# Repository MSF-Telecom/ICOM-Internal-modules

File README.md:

# ICOM Internal modules

A collection of custom internal modules for ICOM IC-F5060/6060 radios.

## Pinouts

The IC-F5060/6060 and IC-F3162T radios have two 40-pin accessory connectors (J1 and J2). They mate with a [Panasonic P5 Series P5K AXK640347YG](https://na.industrial.panasonic.com/products/connectors/board-board-connectors/lineup/narrow-fine-pitch-connectors/series/82696/model/83045) connector.  
You can find a KiCAD Library for J1 and J2 to make your own modules [here](./CAD-Libs/ICOM-J1-J2). The pinouts are as follows (from the service manual) :

### J1

```ascii
           ┌─────╮
      NC   │40  1│   NC
     GND   │39  2│   GND
     +5V   │38  3│   PTTI
     VCC   │37  4│   PTTO
      NC   │36  5│   MCOT
   MMUTI   │35  6│   NC
    AFON   │34  7│   MCIN
    BEPO   │33  8│   NC
    RMUT   │32  9│   NC
    DISC   │31 10│   NC
   AFOUT   │30 11│   NC
      NC   │29 12│   BUSY
     REM   │28 13│   SIGO
     CCS   │27 14│   OPT1/RxD
    CIRQ   │26 15│   OPT2/TxD
      NC   │25 16│   OPT3
     CSO   │24 17│   GND
     CSI   │23 18│   OPV3
     CCK   │22 19│   OPV2
      NC   │21 20│   OPV1
           └─────╯
```

### J2

```ascii
           ┌─────╮
     DIF   │40  1│   DIF
     GND   │39  2│   GND
     +5V   │38  3│   NC
      8V   │37  4│   NC
      NC   │36  5│   NC
      NC   │35  6│   DMO
      NC   │34  7│   NC
      NC   │33  8│   DMI
      NC   │32  9│   NC
    DISC   │31 10│   VREF
      NC   │30 11│   NC
    DAFO   │29 12│   NC
      NC   │28 13│   NC
     CCS   │27 14│   OPT1 (DPDN)
    CIRQ   │26 15│   OPT2 (DRES)
      NC   │25 16│   OPT3 (DRES)
     CSO   │24 17│   GND
     CSI   │23 18│   NC
     CCK   │22 19│   GND
     GND   │21 20│   GND
           └─────╯
```

## Acknowledgements

Made with ❤️, lots of ☕️, and lack of 🛌  
Published under CreativeCommons BY-SA 4.0

This work is licensed under a [Creative Commons Attribution-ShareAlike 4.0 International License](http://creativecommons.org/licenses/by-sa/4.0/).

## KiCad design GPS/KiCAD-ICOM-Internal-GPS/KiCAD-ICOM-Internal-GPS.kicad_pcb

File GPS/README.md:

# GPS Module

All the files and R&D data for a custom GPS module.

## Module Design Specifications

A.  Must have  

  1. UT-126H form factor (20x35mm)
  2. UART NMEA GPS module with 4800/9600 baud rate
  3. 5V Supply compatible
  4. 5V Antenna supply
  5. UFL Antenna connector
  6. Test pads for VCC, GND, TX, RX and PPS

B.  Nice to have

  1. Switchable antenna supply
  2. Backup battery circuitry
  3. Antenna short circuit detection & protection

C.  Optional

  1. Antenna connection detection
  2. Additional 2.54mm pitch header with VCC, GND, UART, PPS and I2C
  3. PPS LED
  4. TX/RX LEDs

## Module Design Choices

### v1.0

#### Requirements

- PCB
  - 2 layer
  - Test pads on user visible side (satisfies A6)
  - 20x35mm form factor (satisfies A1)
  - Silk screen on user visible side with checkable baud rate options
- Connectors
  - UFL Antenna connector (satisfies A5)
  - 2.54mm pitch header with VCC, GND, UART, PPS and I2C (satisfies C2)
- Battery backup with 6.8mm SDM 3V rechargeable lithium cell (satisfies B2)
- GPS Module : [u-blox MAX-M10](https://www.u-blox.com/en/product/max-m10-series?legacy=Current#Documentation-&-resources) (can satisfy A1, A2, A3 with regulator, A4, B1, B2, B3 and C1)
- LEDs on user visible side (satisfies C3 and C4)
- No antenna short circuit detection (does not satisfy B3 or C1)
- Constant 5V antenna supply (satisfies A4, but not B1)

#### Component choice

- [u-blox MAX-M10](https://www.u-blox.com/en/product/max-m10-series?legacy=Current#Documentation-&-resources)
- Battery : [SEIKO INSTRUMENTS MS518SE-FL35E](https://www.farnell.com/datasheets/3115182.pdf) ([Farnell](https://be.farnell.com/en-BE/seiko-instruments/ms518se-fl35e/battery-button-lithium-3-4mah/dp/3534575))
- U.FL : [HIROSE(HRS) U.FL-R-SMT-1(10)](https://www.farnell.com/datasheets/2691132.pdf) ([Farnell](https://be.farnell.com/en-BE/hirose-hrs/u-fl-r-smt-1-10/rf-coaxial-u-fl-straight-jack/dp/1688077))
- C1, C2 : [0603B105K250NT](https://www.lcsc.com/datasheet/lcsc_datasheet_2304140030_FH--Guangdong-Fenghua-Advanced-Tech-0603B105K250NT_C59302.pdf)
- L1 (Antenna supply inductor, 27nH) : [Murata LQG15HS27NJ02D](https://www.mouser.be/datasheet/2/281/1/JELF243B_0010-1699614.pdf)
- C4, C5, C6 (Antenna supply filter, 10nF, 16V, X7R) : [CC0603KRX7R0BB103](https://www.lcsc.com/datasheet/lcsc_datasheet_2304140030_YAGEO-CC0603KRX7R0BB103_C107059.pdf)
- 3.3V Regulator : [SPX5205M5-L-3-3/TR](https://www.lcsc.com/datasheet/lcsc_datasheet_2304140030_MaxLinear-SPX5205M5-L-3-3-TR_C6864.pdf)
- D1 : [RB551V-40](https://www.lcsc.com/datasheet/lcsc_datasheet_2308281443_hongjiacheng-RB551V-40_C7502699.pdf)
- D2 : [KINGBRIGHT KPTR-3216SURCK](https://www.farnell.com/datasheets/2045968.pdf)
- D3 : [XL-3216SURC](https://www.lcsc.com/datasheet/lcsc_datasheet_2402181505_XINGLIGHT-XL-3216SURC_C965822.pdf)
- D4, D5 : [XL-3216UOC](https://www.lcsc.com/datasheet/lcsc_datasheet_2402181505_XINGLIGHT-XL-3216UOC_C965823.pdf)
- R1 : [ERJPA3J100V](https://www.lcsc.com/product-detail/Chip-Resistor-Surface-Mount_PANASONIC-ERJPA3J100V_C441879.html)
- R2, R3, R4 : [CR0603-FX-3301ELF](https://www.lcsc.com/datasheet/lcsc_datasheet_2304140030_BOURNS-CR0603-FX-3301ELF_C203527.pdf)
- R5, R6, R7, R8 : [RC0603JR-07220RL](https://www.lcsc.com/datasheet/lcsc_datasheet_2304140030_YAGEO-RC0603JR-07220RL_C114683.pdf)

#### Cost breakdown

> Cost for one unit at 100pcs MOQ, without PCBA

##### Full prototype with debug LEDs

| Component                                  | Source | Cost ($) | Amount | Total ($) |
|--------------------------------------------|--------|----------|--------|-----------|
| PCB                                        | JLCPCB | 0.141    | 1      | 0.141     |
| LQG15HS27NJ02DLQG15HS27NJ02D 27nH inductor | LCSC   | 0.0065   | 1      | 0.0065    |
| U.FL-R-SMT-1(10) UFL connector             | LCSC   | 0.0.1177 | 1      | 0.1615    |
| SPX5205M5-L-3-3/TR 3.3V LDO regulator      | LCSC   | 0.1209   | 1      | 0.1209    |
| 0603B105K250NT 1uF 25V capacitor           | LCSC   | 0.0053   | 2      | 0.0106    |
| CC0603KRX7R0BB103 10nF 16V capacitor       | LCSC   | 0.0041   | 4      | 0.0164    |
| RC0603JR-07220RL 220 Ohm resistor          | LCSC   | 0.001    | 4      | 0.0040    |
| CR0603-FX-3301ELF 3.3k Ohm resistor        | LCSC   | 0.0062   | 3      | 0.0186    |
| ERJPA3J100V 10 Ohm resistor                | LCSC   | 0.0193   | 1      | 0.0193    |
| APTR3216SURCK Through-PCB LED              | LCSC   | 0.1032   | 1      | 0.1032    |
| MAX-M10S-00B GPS module                    | Mouser | 11.48    | 1      | 11.48     |
| AXK640347YG Connector                      | Mouser | 1.60     | 1      | 1.60      |
| MS518SE-FL35E Battery                      | Farnell| 2.15     | 1      | 2.15      |
| RB551V-40 Diode                            | LCSC   | 0.018    | 1      | 0.018     |
| XL-3216SURC Red LED                        | LCSC   | 0.0082   | 1      | 0.0082    |
| XL-3216UOC Orange LED                      | LCSC   | 0.0092   | 2      | 0.0184    |
|                                            |        |          |        |           |
| **Total**                                  |        |          |        | 15.8766   |

##### Integration prototype with battery backup

| Component                                  | Source | Cost ($) | Amount | Total ($) |
|--------------------------------------------|--------|----------|--------|-----------|
| PCB                                        | JLCPCB | 0.141    | 1      | 0.141     |
| LQG15HS27NJ02DLQG15HS27NJ02D 27nH inductor | LCSC   | 0.0065   | 1      | 0.0065    |
| U.FL-R-SMT-1(10) UFL connector             | LCSC   | 0.0.1177 | 1      | 0.1615    |
| SPX5205M5-L-3-3/TR 3.3V LDO regulator      | LCSC   | 0.1209   | 1      | 0.1209    |
| 0603B105K250NT 1uF 25V capacitor           | LCSC   | 0.0053   | 2      | 0.0106    |
| CC0603KRX7R0BB103 10nF 16V capacitor       | LCSC   | 0.0041   | 4      | 0.0164    |
| RC0603JR-07220RL 220 Ohm resistor          | LCSC   | 0.001    | 1      | 0.0010    |
| CR0603-FX-3301ELF 3.3k Ohm resistor        | LCSC   | 0.0062   | 3      | 0.0186    |
| ERJPA3J100V 10 Ohm resistor                | LCSC   | 0.0193   | 1      | 0.0193    |
| APTR3216SURCK Through-PCB LED              | LCSC   | 0.1032   | 1      | 0.1032    |
| MAX-M10S-00B GPS module                    | Mouser | 11.48    | 1      | 11.48     |
| AXK640347YG Connector                      | Mouser | 1.60     | 1      | 1.60      |
| MS518SE-FL35E Battery                      | Farnell| 2.15     | 1      | 2.15      |
| RB551V-40 Diode                            | LCSC   | 0.018    | 1      | 0.018     |
|                                            |        |          |        |           |
| **Total**                                  |        |          |        | 15.847    |

##### Integration prototype without battery backup

| Component                                  | Source | Cost ($) | Amount | Total ($) |
|--------------------------------------------|--------|----------|--------|-----------|
| PCB                                        | JLCPCB | 0.141    | 1      | 0.141     |
| LQG15HS27NJ02DLQG15HS27NJ02D 27nH inductor | LCSC   | 0.0065   | 1      | 0.0065    |
| U.FL-R-SMT-1(10) UFL connector             | LCSC   | 0.0.1177 | 1      | 0.1615    |
| SPX5205M5-L-3-3/TR 3.3V LDO regulator      | LCSC   | 0.1209   | 1      | 0.1209    |
| 0603B105K250NT 1uF 25V capacitor           | LCSC   | 0.0053   | 2      | 0.0106    |
| CC0603KRX7R0BB103 10nF 16V capacitor       | LCSC   | 0.0041   | 3      | 0.0164    |
| RC0603JR-07220RL 220 Ohm resistor          | LCSC   | 0.001    | 1      | 0.0010    |
| CR0603-FX-3301ELF 3.3k Ohm resistor        | LCSC   | 0.0062   | 2      | 0.0186    |
| ERJPA3J100V 10 Ohm resistor                | LCSC   | 0.0193   | 1      | 0.0193    |
| APTR3216SURCK Through-PCB LED              | LCSC   | 0.1032   | 1      | 0.1032    |
| MAX-M10S-00B GPS module                    | Mouser | 11.48    | 1      | 11.48     |
| AXK640347YG Connector                      | Mouser | 1.60     | 1      | 1.60      |
|                                            |        |          |        |           |
| **Total**                                  |        |          |        | 13.6687   |

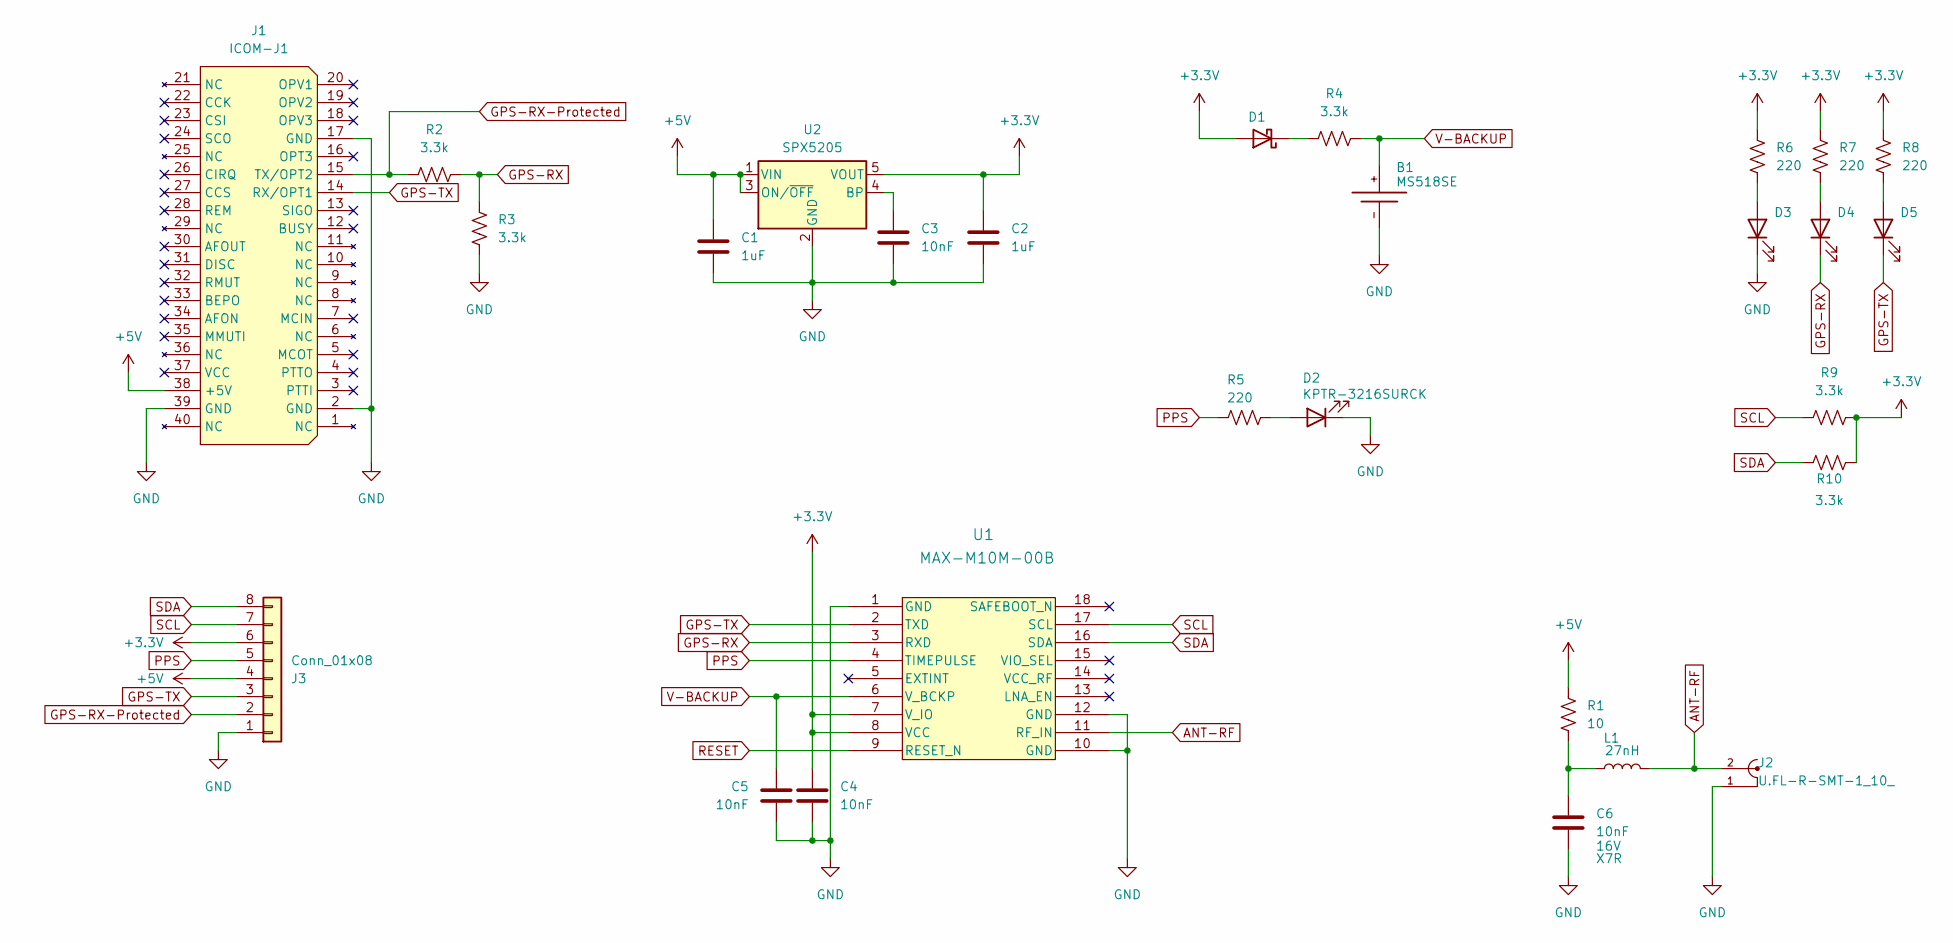
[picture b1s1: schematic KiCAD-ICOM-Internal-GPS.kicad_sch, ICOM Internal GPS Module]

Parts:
B1: MS518SE; MS518SE-FL35E; MPN MS518SE-FL35E; DIGIKEY 728-1054-ND
C1, C2: 1uF; C_0603_1608Metric
C3, C4, C5: 10nF; C_0603_1608Metric
C6: 10nF; C_0603_1608Metric; Voltage rating 16V
D1: RB551V-40; D_SOD-323
D2: KPTR-3216SURCK; LED320X125X130N
D3: XL-3216SURC; LED_1206_3216Metric
D4, D5: XL-3216UOC; LED_1206_3216Metric
J1: ICOM-J1; ICOM-J1-J2; Mouser Part Number 769-AXK640347YG
J2: U.FL-R-SMT-1_10_; HRS_U.FL-R-SMT-1_10_
J3: Conn_01x08; PinSocket_1x08_P2.54mm_Vertical
L1: 27nH; L_0402_1005Metric; Part number LQG15HS27NJ02D
R1: 10; R_0603_1608Metric
R2, R3, R4: 3.3k; R_0603_1608Metric
R5, R6, R7, R8: 220; R_0603_1608Metric_Pad0.98x0.95mm_HandSolder
R9, R10: 3.3k; R_0603_1608Metric_Pad0.98x0.95mm_HandSolder
U1: MAX-M10M-00B; MOD18_MAX-M10M_UBL
U2: SPX5205; SOT-23-5

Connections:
+3.3V: C2.1, C4.1, D1.2 (A), J3.6, R6.1, R7.1, R8.1, R9.2, R10.2, U1.7 (V_IO), U1.8 (VCC), U2.5 (VOUT)
+5V: C1.1, J1.38 (+5V), J3.4, R1.1, U2.1 (VIN), U2.3 (ON/~OFF)
ANT-RF: J2.2, L1.2, U1.11 (RF_IN)
GND: B1.-, C1.2, C2.2, C3.2, C4.2, C5.2, C6.2, D2.2 (K), D3.1 (K), J1.2 (GND), J1.17 (GND), J1.39 (GND), J2.1, J2.3, J3.1, R3.2, U1.1 (GND), U1.10 (GND), U1.12 (GND), U2.2 (GND)
GPS-RX: D4.1 (K), R2.2, R3.1, U1.3 (RXD)
GPS-RX-Protected: J1.15 (TX/OPT2), J3.2, R2.1
GPS-TX: D5.1 (K), J1.14 (RX/OPT1), J3.3, U1.2 (TXD)
unnamed: C6.1, L1.1, R1.2
unnamed: D1.1 (K), R4.1
unnamed: D2.1 (A), R5.2
unnamed: D3.2 (A), R6.2
unnamed: D4.2 (A), R7.2
unnamed: D5.2 (A), R8.2
unnamed: C3.1, U2.4 (BP)
PPS: J3.5, R5.1, U1.4 (TIMEPULSE)
RESET: U1.9 (RESET_N)
SCL: J3.7, R9.1, U1.17 (SCL)
SDA: J3.8, R10.1, U1.16 (SDA)
V-BACKUP: B1.+, C5.1, R4.2, U1.6 (V_BCKP)

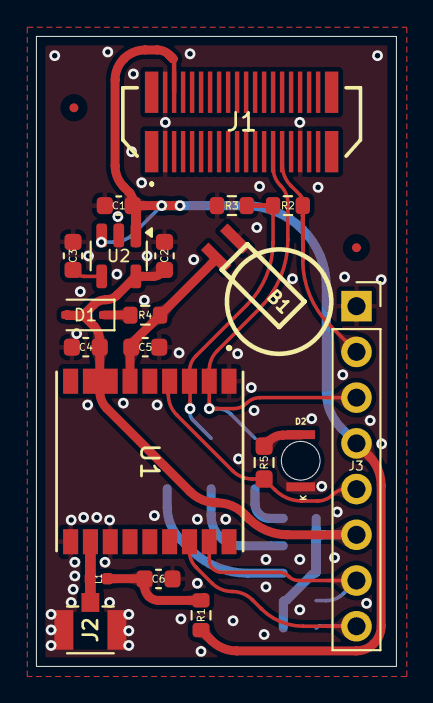
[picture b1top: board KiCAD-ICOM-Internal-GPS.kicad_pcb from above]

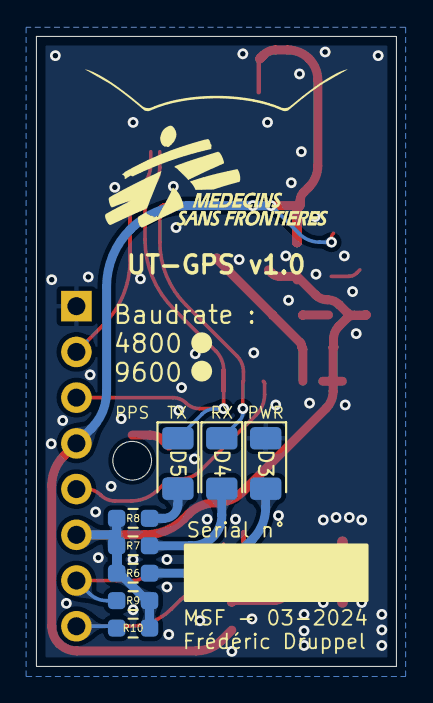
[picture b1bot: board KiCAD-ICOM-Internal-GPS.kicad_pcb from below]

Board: 2 copper layers, 20.0 x 35.0 mm, 30 parts (8 on the bottom side), 18 nets.

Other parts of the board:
F1, F2: Fiducial_0.5mm_Mask1.5mm

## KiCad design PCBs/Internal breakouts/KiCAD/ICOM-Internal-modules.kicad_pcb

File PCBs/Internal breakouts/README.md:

# ICOM Internal Breakouts

## Why

MSF uses a lot of ICOM IC-F5000 series radios in the field. These are VHF FM radios that can be upgraded with an internal module to work as a dPMR or NXDN radios.  
We wanted to explore the capabilities of these internal expansion connectors and see if we could use them to interface with other devices (for example an FSK modulator for pagers).

In order to do some prototyping, and after trying to solder tiny wires on the tiny pads of the PCB, I decided to design a breakout board that would make it easier to interface with the radio.

After finding the correct connectors, I designed a PCB that would fit in the radio and expose the internal connectors to more standard 2.54mm pitch headers.  
The connectors for J1 and J2 are the same, but the pinout is different as J2 is intended for DSPs like the UT-126H.

I also added a connector for the internal GPS connector, as the radio can transmit GPS positions with an *external* or *internal* GPS receiver, but I've never seen the internal GPS receiver and wanted to see if it was feasable.

## BOM

* Mating connectors for J1 and J2 : [Panasonic P5 Series P5K AXK640347YG](https://na.industrial.panasonic.com/products/connectors/board-board-connectors/lineup/narrow-fine-pitch-connectors/series/82696/model/83045)
* Mating connector for 0.8mm pitch GPS connector : [Samtec FTE-105-01-G-DV](https://www.samtec.com/products/fte)
* 4x 1x10 2.54mm pitch headers
* 1x 2x5 2.54mm pitch header

## PCBs

Here are some 3D renders of the PCBs :

> Note : Gerber files exported with default settings, you might want to re-export from KiCAD depending on your PCB manufacturer

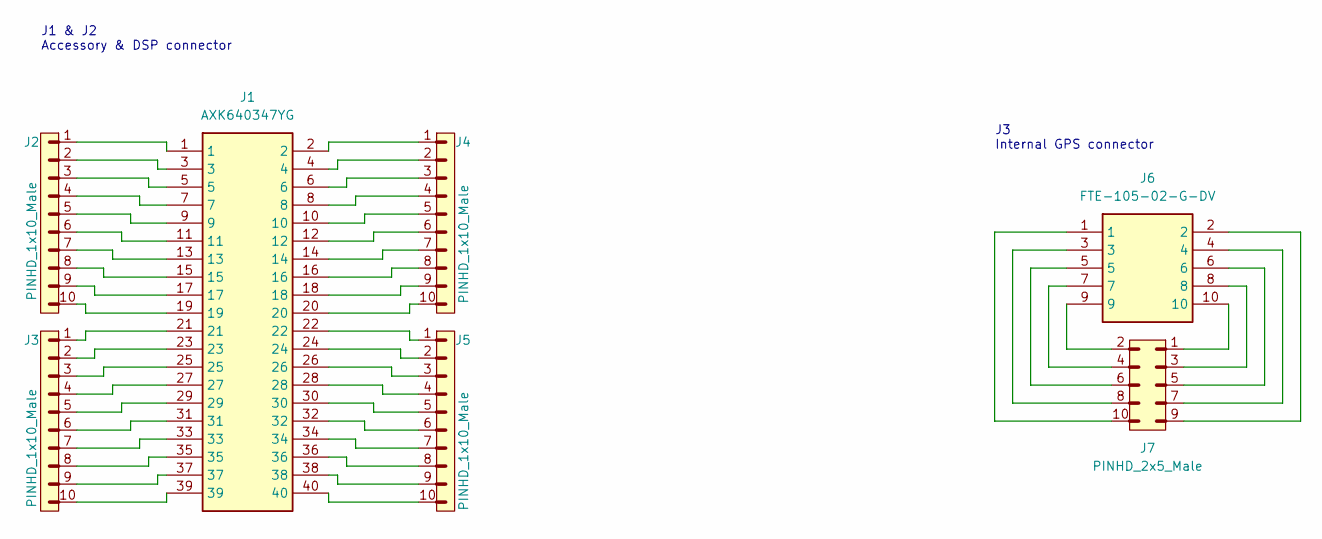
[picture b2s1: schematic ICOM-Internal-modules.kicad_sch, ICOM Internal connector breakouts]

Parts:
J1: AXK640347YG; Mouser Part Number 769-AXK640347YG
J2, J3, J4, J5: PINHD_1x10_Male; PinHeader_1x10_P2.54mm_Vertical
J6: FTE-105-02-G-DV; FTE-105-XX-G-DV; Mouser Part Number 200-FTE10502GDV
J7: PINHD_2x5_Male; PinHeader_2x05_P2.54mm_Vertical

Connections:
unnamed: J1.1, J2.1
unnamed: J1.2, J4.1
unnamed: J1.3, J2.2
unnamed: J1.4, J4.2
unnamed: J1.5, J2.3
unnamed: J1.6, J4.3
unnamed: J1.7, J2.4
unnamed: J1.8, J4.4
unnamed: J1.9, J2.5
unnamed: J1.10, J4.5
unnamed: J1.11, J2.6
unnamed: J1.12, J4.6
unnamed: J1.13, J2.7
unnamed: J1.14, J4.7
unnamed: J1.15, J2.8
unnamed: J1.16, J4.8
unnamed: J1.17, J2.9
unnamed: J1.18, J4.9
unnamed: J1.19, J2.10
unnamed: J1.20, J4.10
unnamed: J1.21, J3.1
unnamed: J1.22, J5.1
unnamed: J1.23, J3.2
unnamed: J1.24, J5.2
unnamed: J1.25, J3.3
unnamed: J1.26, J5.3
unnamed: J1.27, J3.4
unnamed: J1.28, J5.4
unnamed: J1.29, J3.5
unnamed: J1.30, J5.5
unnamed: J1.31, J3.6
unnamed: J1.32, J5.6
unnamed: J1.33, J3.7
unnamed: J1.34, J5.7
unnamed: J1.35, J3.8
unnamed: J1.36, J5.8
unnamed: J1.37, J3.9
unnamed: J1.38, J5.9
unnamed: J1.39, J3.10
unnamed: J1.40, J5.10
unnamed: J6.1, J7.10
unnamed: J6.2, J7.9
unnamed: J6.3, J7.8
unnamed: J6.4, J7.7
unnamed: J6.5, J7.6
unnamed: J6.6, J7.5
unnamed: J6.7, J7.4
unnamed: J6.8, J7.3
unnamed: J6.9, J7.2
unnamed: J6.10, J7.1

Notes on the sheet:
J1 & J2 Accessory & DSP connector
J3 Internal GPS connector

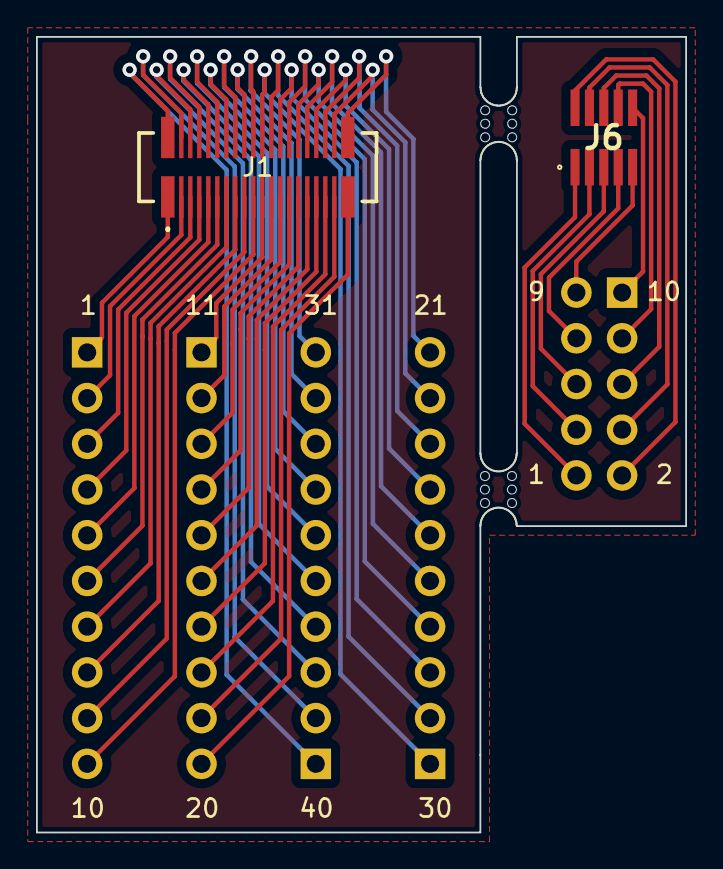
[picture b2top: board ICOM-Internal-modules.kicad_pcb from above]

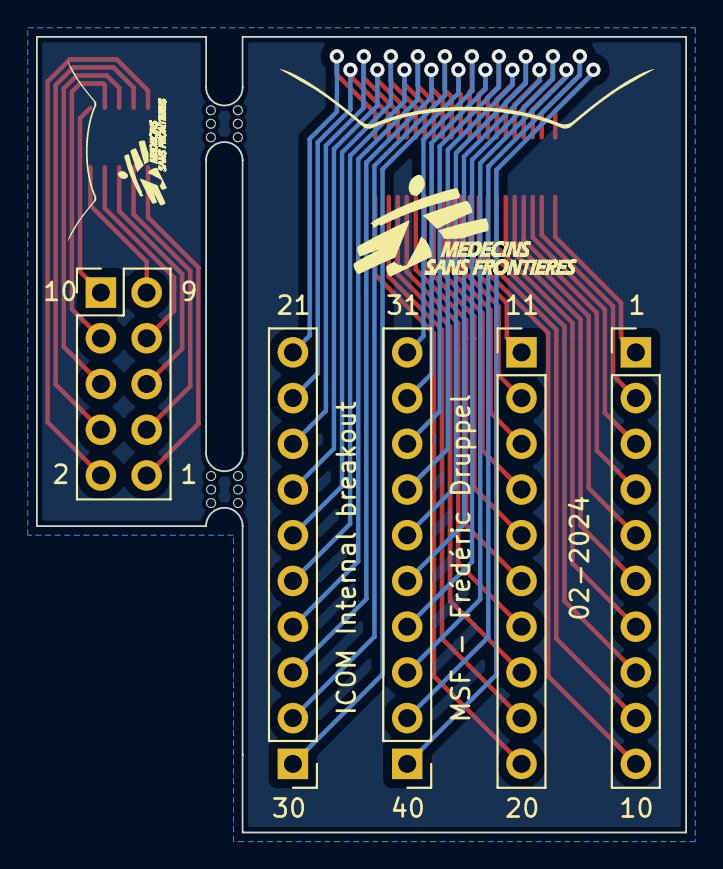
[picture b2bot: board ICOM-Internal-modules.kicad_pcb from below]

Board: 2 copper layers, 36.1 x 44.2 mm, 9 parts (5 on the bottom side), 50 nets.

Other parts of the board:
mouse-bite-2mm-slot, mouse-bite-2mm-slot#2: VAL**; mouse-bite-2mm-slot

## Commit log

2024-02-15 added trinity files
2024-02-15 added breakout files
2024-02-15 added descriptions
2024-02-22 added GPS data dump
2024-02-22 moved file
2024-02-22 added info file
2024-02-22 added readme
2024-02-22 added NEO-8M data
2024-03-11 added KiCAD stuff to gitignore
2024-03-11 added base files for ICOM Internal GPS
2024-03-11 added CAD Libs for some components
2024-03-11 added libs
2024-03-11 updated KiCAD files
2024-03-11 added ICOM J1 Connector library same as AXK640347YG, except with the right pin names
2024-03-11 updated schematic & PCB
2024-03-12 updated ICOM J1/J2 library
2024-03-12 added J1/J2 Pinouts
2024-03-12 added stuff to gitignore
2024-03-12 updated schematic a bit
2024-03-12 did some formatting
2024-03-12 updated footer
2024-03-12 added module design specifications
2024-03-12 added design choices
2024-03-12 made minor changes to requirements and decisions
2024-03-12 updated libs
2024-03-12 updated v1.0 design
2024-03-12 updated MAX-M10 3D model
2024-03-12 minor save
2024-03-15 added component specifications
2024-03-15 added to gitignore
2024-03-15 updated schematic and pcb
2024-03-16 added LED CAD lib
2024-03-16 Routed traces
2024-03-16 fixed markdownlint error
2024-03-24 saved changes from KiCAD
2024-03-24 updated components
2024-03-25 Add GPS schematics, gerber files, and component information
2024-04-11 added cost breakdown
2024-04-11 fixed markdown error
2024-04-11 added PCB to cost

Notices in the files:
README.md:
CC BY-SA 4.0
